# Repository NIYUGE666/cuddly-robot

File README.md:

# 波形合成电路 / Waveform Synthesis Circuit

NE555 + TL082，外接 ±12 V。NE555 产生约 2 kHz 时钟，经 CD4013 二分频、隔直和缓冲后得到可校准的 1 kHz、10 Vpp 方波。四路分别提取 1/3/5/7 kHz，调幅、移相后相加。

**Rev B 是已通过本地检查、需要实物校准的设计版本；尚未在嘉立创 EDA 专业版中实际导入验证。** 提供自包含 KiCad 可编辑源文件及 EAGLE XML 交换文件，不冒充嘉立创原生 `.epro` 工程。

| 文件 | 用途 |
|---|---|
| [导入说明](docs/IMPORT_EASYEDA_PRO.md) | 两种交换包、导入后核对项目、版本限制 |
| [设计及校准说明](docs/DESIGN.md) | 电路公式、元件参数、接口、22 个电位器的调试步骤 |
| [验证记录](docs/VALIDATION.md) | 已完成、自动通过、待验证及已知限制 |
| [原理图 PDF](docs/schematic.pdf) | 单张 A0 功能分区图；信号路径用实际导线连接 |
| [PCB 预览](docs/pcb.svg) | 双层，229 × 231 mm，全部插件安装 |
| [BOM](hardware/BOM.csv) / [分组 BOM](hardware/BOM_grouped.csv) | 逐项和采购分组；无未经核对的立创商品编号 |
| [KiCad 工程](hardware/waveform.kicad_pro) | KiCad 9.0.2；打开同目录的主原理图和 PCB |
| [EAGLE 原理图](hardware/waveform.sch) / [PCB](hardware/waveform.brd) | XML 交换格式，元件库内嵌 |
| [release](release/) | 两种导入 ZIP、制板输出 ZIP、校验和 |

Rev B 修正了旧版按元件清单排成网格的原理图：按信号流向排列四个通道，将 TL082 拆分为 A/B 放大单元和独立电源单元。PCB 铜线、过孔、封装位置和器件编号不变；根网络名称增加 `/` 前缀是 KiCad 单页局部网命名规则。

自动检查：ERC、DRC、未连接项、原理图/PCB 一致性均为 0 项；190 个封装、491 个引脚核对一致。EAGLE PCB 经 KiCad 的实际 EAGLE 导入器回读，489 个已连接引脚保持一致；2 个 CD4013 备用输出明确不连接。详细证据见 `validation/`。

波形计算采用 TL082 单极点近似，而非厂家 SPICE 模型或实测。四项傅里叶合成有 Gibbs 过冲，源方波 10 Vpp 对应的合成输出约 11.84 Vpp；如需要合成输出也恰为 10 Vpp，可统一缩放四路幅度，但不能消除有限谐波的过冲。

复现环境：系统 Python 3 + `pcbnew`、KiCad CLI 9、g++；分析脚本使用 Python 的 numpy/scipy/matplotlib。运行 `tools/validate.sh` 检查已有设计。**`tools/rebuild.sh` 会重新生成并覆盖本项目的生成文件，仅在确认没有手工编辑后使用。** 现有云任务已经隔离，无需另建 Git worktree。

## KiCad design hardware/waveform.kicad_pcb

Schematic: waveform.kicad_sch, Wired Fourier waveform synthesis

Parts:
C1, C2, C4, C5, C6, C7, C8, C9: 10n; C_Disc_D5.0mm_W2.5mm_P5.00mm
C3: 10u/25V; CP_Radial_D5.0mm_P2.00mm
C10, C11, C12, C13, C14, C15: 3.3n; C_Disc_D5.0mm_W2.5mm_P5.00mm
C16, C17, C18, C19, C20, C21: 2n; C_Disc_D5.0mm_W2.5mm_P5.00mm
C22, C23, C24, C25, C26, C27: 1.5n; C_Disc_D5.0mm_W2.5mm_P5.00mm
C28, C29: 47u/25V; CP_Radial_D5.0mm_P2.00mm
C30, C31, C32, C33, C34, C35, C36, C37, C38, C39, C40, C41, C42, C43, C44, C45, C46, C47, C48, C49, C50, C51, C52, C53, C54, C55, C56, C57, C58, C59: 100n; C_Disc_D5.0mm_W2.5mm_P5.00mm
J1, J2, J3, J4: PHASE_POLARITY; PinHeader_1x03_P2.54mm_Vertical
J5: POWER_12V; PinHeader_1x03_P2.54mm_Vertical
J6: WAVE_OUT; PinHeader_1x02_P2.54mm_Vertical
R1, R12, R13, R15, R16, R18, R19, R26, R27, R29, R30, R32, R33, R40, R41, R43, R44, R46, R47, R54, R55, R57, R58, R60, R61: 10k; R_Axial_DIN0207_L6.3mm_D2.5mm_P7.62mm_Horizontal
R2: 27k; R_Axial_DIN0207_L6.3mm_D2.5mm_P7.62mm_Horizontal
R3: 1M; R_Axial_DIN0207_L6.3mm_D2.5mm_P7.62mm_Horizontal
R4, R5, R62, R63, R64, R65, R66, R67, R68: 100k; R_Axial_DIN0207_L6.3mm_D2.5mm_P7.62mm_Horizontal
R6, R9, R20, R23, R34, R37, R48, R51: 220k; R_Axial_DIN0207_L6.3mm_D2.5mm_P7.62mm_Horizontal
R7, R10, R21, R24, R35, R38, R49, R52: 430; R_Axial_DIN0207_L6.3mm_D2.5mm_P7.62mm_Horizontal
R8, R11, R22, R25, R36, R39, R50, R53: 470k; R_Axial_DIN0207_L6.3mm_D2.5mm_P7.62mm_Horizontal
R14, R17, R28, R31, R42, R45, R56, R59, R69: 100; R_Axial_DIN0207_L6.3mm_D2.5mm_P7.62mm_Horizontal
RV1: 20k; Potentiometer_Bourns_3296W_Vertical
RV2: 100k; Potentiometer_Bourns_3296W_Vertical
RV3, RV4, RV8, RV9, RV13, RV14, RV18, RV19: 200; Potentiometer_Bourns_3296W_Vertical
RV5, RV6, RV10, RV11, RV15, RV16, RV20, RV21: 200k; Potentiometer_Bourns_3296W_Vertical
RV7, RV12, RV17, RV22: 10k; Potentiometer_Bourns_3296W_Vertical
TP1: CLOCK_2K; TestPoint_THTPad_D1.5mm_Drill0.7mm
TP2: SQ; TestPoint_THTPad_D1.5mm_Drill0.7mm
TP3: SQ_INV; TestPoint_THTPad_D1.5mm_Drill0.7mm
TP4: H1_BPF2; TestPoint_THTPad_D1.5mm_Drill0.7mm
TP5: H1_AP2; TestPoint_THTPad_D1.5mm_Drill0.7mm
TP6: H1_OUT; TestPoint_THTPad_D1.5mm_Drill0.7mm
TP7: H3_BPF2; TestPoint_THTPad_D1.5mm_Drill0.7mm
TP8: H3_AP2; TestPoint_THTPad_D1.5mm_Drill0.7mm
TP9: H3_OUT; TestPoint_THTPad_D1.5mm_Drill0.7mm
TP10: H5_BPF2; TestPoint_THTPad_D1.5mm_Drill0.7mm
TP11: H5_AP2; TestPoint_THTPad_D1.5mm_Drill0.7mm
TP12: H5_OUT; TestPoint_THTPad_D1.5mm_Drill0.7mm
TP13: H7_BPF2; TestPoint_THTPad_D1.5mm_Drill0.7mm
TP14: H7_AP2; TestPoint_THTPad_D1.5mm_Drill0.7mm
TP15: H7_OUT; TestPoint_THTPad_D1.5mm_Drill0.7mm
TP16: SUM_RAW; TestPoint_THTPad_D1.5mm_Drill0.7mm
TP17: OUT; TestPoint_THTPad_D1.5mm_Drill0.7mm
TP18: GND; TestPoint_THTPad_D1.5mm_Drill0.7mm
U1: NE555P; DIP-8_W7.62mm
U2: CD4013BE; DIP-14_W7.62mm
U3, U4, U5, U6, U7, U8, U9, U10, U11, U12, U13, U14, U15, U16: TL082CP; DIP-8_W7.62mm

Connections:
/AC_SQUARE: C3.2 (-), R3.1, RV2.1
/CLOCK_2K: TP1.1, U1.3 (OUT), U2.3 (CLK1)
/CTRL: C2.1, U1.5 (CTRL)
/DIGITAL_1K: C3.1 (+), U2.1 (Q1)
/DISCHARGE: R1.2, R2.1, U1.7 (DISCH)
/D_FEEDBACK: U2.2 (~Q1), U2.5 (D1)
/FREQ_R: R2.2, RV1.1
/GND: C1.2, C2.2, C8.2, C9.2, C14.2, C15.2, C20.2, C21.2, C26.2, C27.2, C28.2 (-), C29.1 (+), C30.2, C31.2, C32.2, C33.1, C34.2, C35.1, C36.2, C37.1, C38.2, C39.1, C40.2, C41.1, C42.2, C43.1, C44.2, C45.1, C46.2, C47.1, C48.2, C49.1, C50.2, C51.1, C52.2, C53.1, C54.2, C55.1, C56.2, C57.1, C58.2, C59.1, J5.2, J6.2, R3.2, RV2.3, RV3.2 (W), RV3.3, RV4.2 (W), RV4.3, RV7.3, RV8.2 (W), RV8.3, RV9.2 (W), RV9.3, RV12.3, RV13.2 (W), RV13.3, RV14.2 (W), RV14.3, RV17.3, RV18.2 (W), RV18.3, RV19.2 (W), RV19.3, RV22.3, TP18.1, U1.1 (GND), U2.4 (RESET1), U2.6 (SET1), U2.7 (VSS), U2.8 (SET2), U2.9 (D2), U2.11 (CLK2), U3.5 (+), U4.3 (+), U4.5 (+), U6.3 (+), U7.3 (+), U7.5 (+), U9.3 (+), U10.3 (+), U10.5 (+), U12.3 (+), U13.3 (+), U13.5 (+), U15.3 (+), U16.3 (+), U16.5 (+)
/H1_AMPLITUDE: RV7.2 (W), U6.5 (+)
/H1_AP1: R13.1, R15.1, R17.1, U5.1 (OUT)
/H1_AP2: J1.1, R16.1, R18.1, TP5.1, U5.7 (OUT)
/H1_APINV1: R12.2, R13.2, U5.2 (-)
/H1_APINV2: R15.2, R16.2, U5.6 (-)
/H1_BPF1: C4.2, R8.1, R9.1, U4.1 (OUT)
/H1_BPF2: C6.2, R11.1, R12.1, R14.1, TP4.1, U4.7 (OUT)
/H1_INV1: C5.2, R8.2, U4.2 (-)
/H1_INV2: C7.2, R11.2, U4.6 (-)
/H1_LP1: C8.1, RV5.2 (W), RV5.3, U5.3 (+)
/H1_LP2: C9.1, RV6.2 (W), RV6.3, U5.5 (+)
/H1_NEG: J1.3, R19.1, U6.1 (OUT)
/H1_NODE1: C4.1, C5.1, R6.2, R7.1
/H1_NODE2: C6.1, C7.1, R9.2, R10.1
/H1_OUT: R62.1, TP6.1, U6.6 (-), U6.7 (OUT)
/H1_PHR1: R14.2, RV5.1
/H1_PHR2: R17.2, RV6.1
/H1_POLINV: R18.2, R19.2, U6.2 (-)
/H1_SELECT: J1.2, RV7.1
/H1_TUNE1: R7.2, RV3.1
/H1_TUNE2: R10.2, RV4.1
/H3_AMPLITUDE: RV12.2 (W), U9.5 (+)
/H3_AP1: R27.1, R29.1, R31.1, U8.1 (OUT)
/H3_AP2: J2.1, R30.1, R32.1, TP8.1, U8.7 (OUT)
/H3_APINV1: R26.2, R27.2, U8.2 (-)
/H3_APINV2: R29.2, R30.2, U8.6 (-)
/H3_BPF1: C10.2, R22.1, R23.1, U7.1 (OUT)
/H3_BPF2: C12.2, R25.1, R26.1, R28.1, TP7.1, U7.7 (OUT)
/H3_INV1: C11.2, R22.2, U7.2 (-)
/H3_INV2: C13.2, R25.2, U7.6 (-)
/H3_LP1: C14.1, RV10.2 (W), RV10.3, U8.3 (+)
/H3_LP2: C15.1, RV11.2 (W), RV11.3, U8.5 (+)
/H3_NEG: J2.3, R33.1, U9.1 (OUT)
/H3_NODE1: C10.1, C11.1, R20.2, R21.1
/H3_NODE2: C12.1, C13.1, R23.2, R24.1
/H3_OUT: R63.1, TP9.1, U9.6 (-), U9.7 (OUT)
/H3_PHR1: R28.2, RV10.1
/H3_PHR2: R31.2, RV11.1
/H3_POLINV: R32.2, R33.2, U9.2 (-)
/H3_SELECT: J2.2, RV12.1
/H3_TUNE1: R21.2, RV8.1
/H3_TUNE2: R24.2, RV9.1
/H5_AMPLITUDE: RV17.2 (W), U12.5 (+)
/H5_AP1: R41.1, R43.1, R45.1, U11.1 (OUT)
/H5_AP2: J3.1, R44.1, R46.1, TP11.1, U11.7 (OUT)
/H5_APINV1: R40.2, R41.2, U11.2 (-)
/H5_APINV2: R43.2, R44.2, U11.6 (-)
/H5_BPF1: C16.2, R36.1, R37.1, U10.1 (OUT)
/H5_BPF2: C18.2, R39.1, R40.1, R42.1, TP10.1, U10.7 (OUT)
/H5_INV1: C17.2, R36.2, U10.2 (-)
/H5_INV2: C19.2, R39.2, U10.6 (-)
/H5_LP1: C20.1, RV15.2 (W), RV15.3, U11.3 (+)
/H5_LP2: C21.1, RV16.2 (W), RV16.3, U11.5 (+)
/H5_NEG: J3.3, R47.1, U12.1 (OUT)
/H5_NODE1: C16.1, C17.1, R34.2, R35.1
/H5_NODE2: C18.1, C19.1, R37.2, R38.1
/H5_OUT: R64.1, TP12.1, U12.6 (-), U12.7 (OUT)
/H5_PHR1: R42.2, RV15.1
/H5_PHR2: R45.2, RV16.1
/H5_POLINV: R46.2, R47.2, U12.2 (-)
/H5_SELECT: J3.2, RV17.1
/H5_TUNE1: R35.2, RV13.1
/H5_TUNE2: R38.2, RV14.1
/H7_AMPLITUDE: RV22.2 (W), U15.5 (+)
/H7_AP1: R55.1, R57.1, R59.1, U14.1 (OUT)
/H7_AP2: J4.1, R58.1, R60.1, TP14.1, U14.7 (OUT)
/H7_APINV1: R54.2, R55.2, U14.2 (-)
/H7_APINV2: R57.2, R58.2, U14.6 (-)
/H7_BPF1: C22.2, R50.1, R51.1, U13.1 (OUT)
/H7_BPF2: C24.2, R53.1, R54.1, R56.1, TP13.1, U13.7 (OUT)
/H7_INV1: C23.2, R50.2, U13.2 (-)
/H7_INV2: C25.2, R53.2, U13.6 (-)
/H7_LP1: C26.1, RV20.2 (W), RV20.3, U14.3 (+)
/H7_LP2: C27.1, RV21.2 (W), RV21.3, U14.5 (+)
/H7_NEG: J4.3, R61.1, U15.1 (OUT)
/H7_NODE1: C22.1, C23.1, R48.2, R49.1
/H7_NODE2: C24.1, C25.1, R51.2, R52.1
/H7_OUT: R65.1, TP15.1, U15.6 (-), U15.7 (OUT)
/H7_PHR1: R56.2, RV20.1
/H7_PHR2: R59.2, RV21.1
/H7_POLINV: R60.2, R61.2, U15.2 (-)
/H7_SELECT: J4.2, RV22.1
/H7_TUNE1: R49.2, RV18.1
/H7_TUNE2: R52.2, RV19.1
/OUT: J6.1, R69.2, TP17.1
/RESTORE_INV: R67.2, R68.2, U16.6 (-)
/SOURCE_WIPER: RV2.2 (W), U3.3 (+)
/SQ: R4.1, R6.1, R20.1, R34.1, R48.1, TP2.1, U3.1 (OUT), U3.2 (-)
/SQ_INV: R5.1, TP3.1, U3.7 (OUT)
/SQ_INV_IN: R4.2, R5.2, U3.6 (-)
/SUM_INV: R62.2, R63.2, R64.2, R65.2, R66.2, U16.2 (-)
/SUM_NEG: R66.1, R67.1, U16.1 (OUT)
/SUM_RAW: R68.1, R69.1, TP16.1, U16.7 (OUT)
/TIMING: C1.1, RV1.2 (W), RV1.3, U1.2 (TRIG), U1.6 (THRES)
/VCC: C28.1 (+), C30.1, C31.1, C32.1, C34.1, C36.1, C38.1, C40.1, C42.1, C44.1, C46.1, C48.1, C50.1, C52.1, C54.1, C56.1, C58.1, J5.1, R1.1, U1.4 (RESET), U1.8 (VCC), U2.10 (RESET2), U2.14 (VDD), U3.8 (V+), U4.8 (V+), U5.8 (V+), U6.8 (V+), U7.8 (V+), U8.8 (V+), U9.8 (V+), U10.8 (V+), U11.8 (V+), U12.8 (V+), U13.8 (V+), U14.8 (V+), U15.8 (V+), U16.8 (V+)
/VEE: C29.2 (-), C33.2, C35.2, C37.2, C39.2, C41.2, C43.2, C45.2, C47.2, C49.2, C51.2, C53.2, C55.2, C57.2, C59.2, J5.3, U3.4 (V-), U4.4 (V-), U5.4 (V-), U6.4 (V-), U7.4 (V-), U8.4 (V-), U9.4 (V-), U10.4 (V-), U11.4 (V-), U12.4 (V-), U13.4 (V-), U14.4 (V-), U15.4 (V-), U16.4 (V-)

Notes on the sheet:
NE555 + TL082 FOURIER WAVEFORM SYNTHESIS — Rev B wired schematic
Regulated +12 V / GND / -12 V. Signal wires are drawn explicitly. All labels are single-sheet local nets.
SOURCE: 2 kHz clock / divide by two / DC blocking / 10 Vpp calibration
1 kHz: TWO MFB BANDPASS SECTIONS -> TWO ALL-PASS SECTIONS -> POLARITY -> AMPLITUDE
ONE shunt: default 2-3
3 kHz: TWO MFB BANDPASS SECTIONS -> TWO ALL-PASS SECTIONS -> POLARITY -> AMPLITUDE
5 kHz: TWO MFB BANDPASS SECTIONS -> TWO ALL-PASS SECTIONS -> POLARITY -> AMPLITUDE
7 kHz: TWO MFB BANDPASS SECTIONS -> TWO ALL-PASS SECTIONS -> POLARITY -> AMPLITUDE
SUM AND OUTPUT
REGULATED +/-12 V INPUT
C29 positive terminal = GND
ANALOG POWER AND LOCAL BYPASS: 100 nF at each supply pin

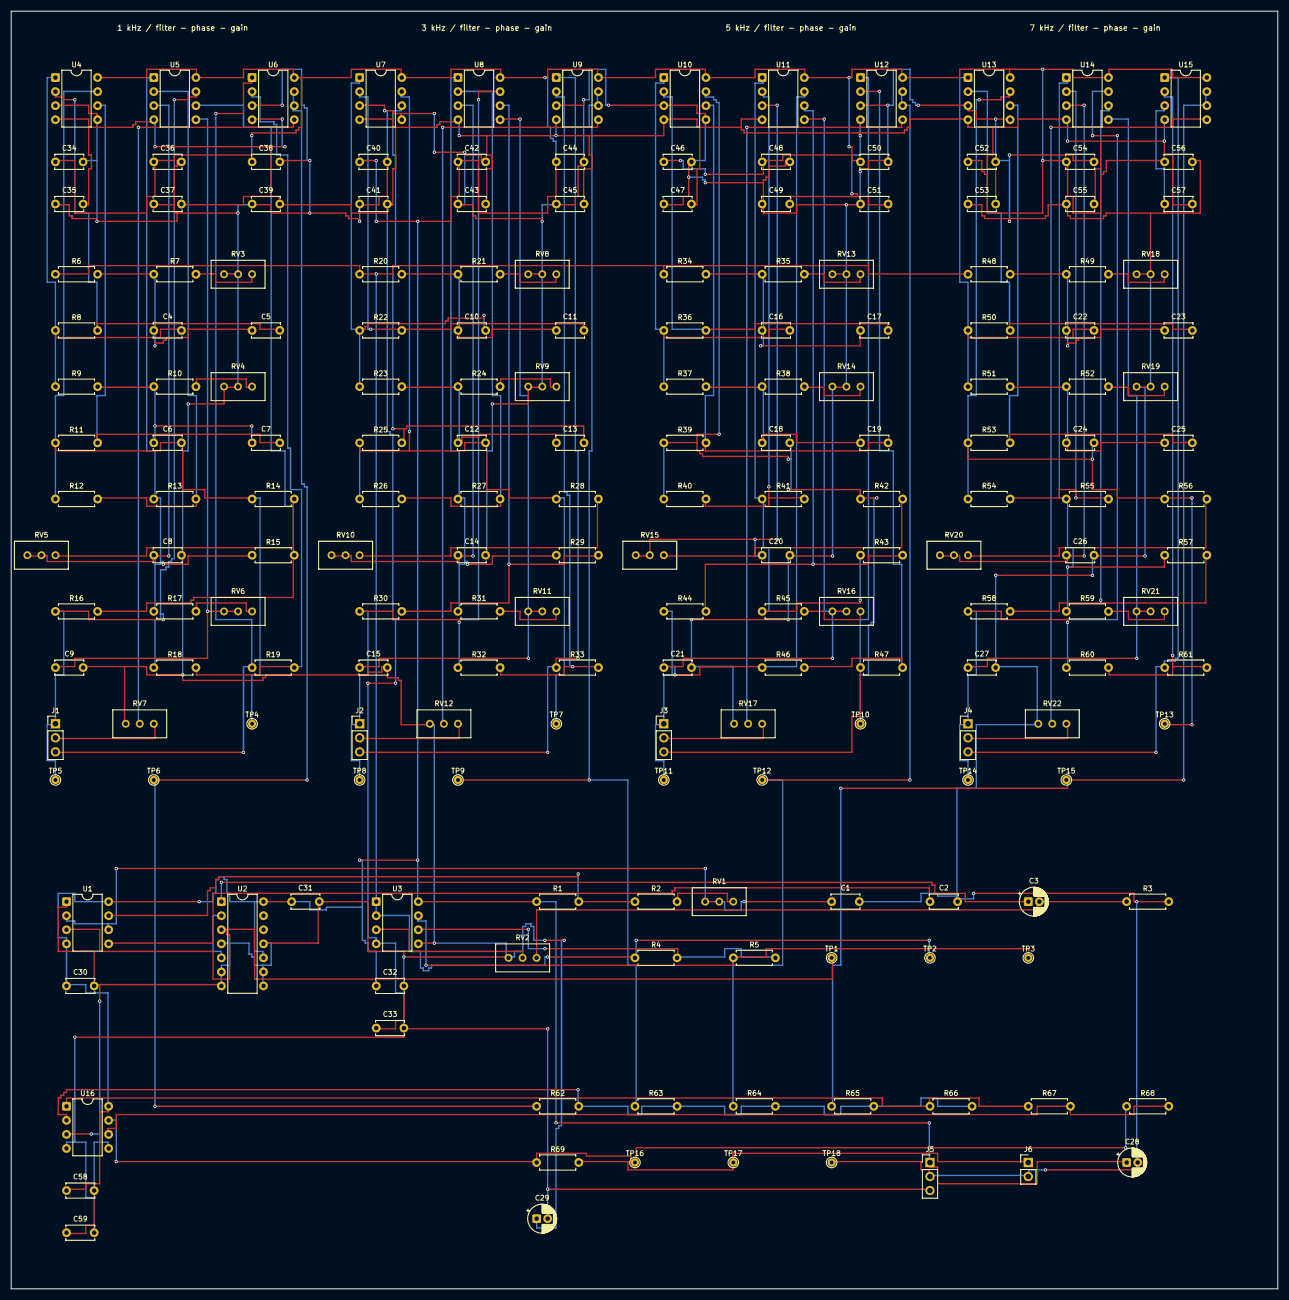
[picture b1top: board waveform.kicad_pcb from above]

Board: 2 copper layers, 229.0 x 231.0 mm, 190 parts (0 on the bottom side), 104 nets.

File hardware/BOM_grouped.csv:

References,Quantity,Value,Type,Footprint,Purchasing_notes
U2,1,CD4013BE,4013,Waveform:DIP-14_W7.62mm,"Through-hole DIP, 7.62mm row spacing; do not substitute a different pinout"
C22 C23 C24 C25 C26 C27,6,1.5n,C,Waveform:C_Disc_D5.0mm_W2.5mm_P5.00mm,5mm pitch; BPF/all-pass: 1% C0G/film; bypass: X7R permitted
C30 C31 C32 C33 C34 C35 C36 C37 C38 C39 C40 C41 C42 C43 C44 C45 C46 C47 C48 C49 C50 C51 C52 C53 C54 C55 C56 C57 C58 C59,30,100n,C,Waveform:C_Disc_D5.0mm_W2.5mm_P5.00mm,5mm pitch; BPF/all-pass: 1% C0G/film; bypass: X7R permitted
C1 C2 C4 C5 C6 C7 C8 C9,8,10n,C,Waveform:C_Disc_D5.0mm_W2.5mm_P5.00mm,5mm pitch; BPF/all-pass: 1% C0G/film; bypass: X7R permitted
C16 C17 C18 C19 C20 C21,6,2n,C,Waveform:C_Disc_D5.0mm_W2.5mm_P5.00mm,5mm pitch; BPF/all-pass: 1% C0G/film; bypass: X7R permitted
C10 C11 C12 C13 C14 C15,6,3.3n,C,Waveform:C_Disc_D5.0mm_W2.5mm_P5.00mm,5mm pitch; BPF/all-pass: 1% C0G/film; bypass: X7R permitted
J6,1,WAVE_OUT,CONN2,Waveform:PinHeader_1x02_P2.54mm_Vertical,2.54mm through-hole header; phase headers additionally require ONE shunt each
J1 J2 J3 J4,4,PHASE_POLARITY,CONN3,Waveform:PinHeader_1x03_P2.54mm_Vertical,2.54mm through-hole header; phase headers additionally require ONE shunt each
J5,1,POWER_12V,CONN3,Waveform:PinHeader_1x03_P2.54mm_Vertical,2.54mm through-hole header; phase headers additionally require ONE shunt each
C3,1,10u/25V,CP,Waveform:CP_Radial_D5.0mm_P2.00mm,"25V minimum, D5mm P2mm; verify purchased body diameter and polarity"
C28 C29,2,47u/25V,CP,Waveform:CP_Radial_D5.0mm_P2.00mm,"25V minimum, D5mm P2mm; verify purchased body diameter and polarity"
U1,1,NE555P,NE555,Waveform:DIP-8_W7.62mm,"Through-hole DIP, 7.62mm row spacing; do not substitute a different pinout"
RV2,1,100k,POT,Waveform:Potentiometer_Bourns_3296W_Vertical,"Bourns 3296W vertical, value code 104; verify pinout 1/2(wiper)/3"
RV7 RV12 RV17 RV22,4,10k,POT,Waveform:Potentiometer_Bourns_3296W_Vertical,"Bourns 3296W vertical, value code 103; verify pinout 1/2(wiper)/3"
RV3 RV4 RV8 RV9 RV13 RV14 RV18 RV19,8,200,POT,Waveform:Potentiometer_Bourns_3296W_Vertical,"Bourns 3296W vertical, value code 201; verify pinout 1/2(wiper)/3"
RV5 RV6 RV10 RV11 RV15 RV16 RV20 RV21,8,200k,POT,Waveform:Potentiometer_Bourns_3296W_Vertical,"Bourns 3296W vertical, value code 204; verify pinout 1/2(wiper)/3"
RV1,1,20k,POT,Waveform:Potentiometer_Bourns_3296W_Vertical,"Bourns 3296W vertical, value code 203; verify pinout 1/2(wiper)/3"
R14 R17 R28 R31 R42 R45 R56 R59 R69,9,100,R,Waveform:R_Axial_DIN0207_L6.3mm_D2.5mm_P7.62mm_Horizontal,"DIN0207 7.62mm pitch; 0.1% recommended for matched gains, 1% otherwise"
R4 R5 R62 R63 R64 R65 R66 R67 R68,9,100k,R,Waveform:R_Axial_DIN0207_L6.3mm_D2.5mm_P7.62mm_Horizontal,"DIN0207 7.62mm pitch; 0.1% recommended for matched gains, 1% otherwise"
R1 R12 R13 R15 R16 R18 R19 R26 R27 R29 R30 R32 R33 R40 R41 R43 R44 R46 R47 R54 R55 R57 R58 R60 R61,25,10k,R,Waveform:R_Axial_DIN0207_L6.3mm_D2.5mm_P7.62mm_Horizontal,"DIN0207 7.62mm pitch; 0.1% recommended for matched gains, 1% otherwise"
R3,1,1M,R,Waveform:R_Axial_DIN0207_L6.3mm_D2.5mm_P7.62mm_Horizontal,"DIN0207 7.62mm pitch; 0.1% recommended for matched gains, 1% otherwise"
R6 R9 R20 R23 R34 R37 R48 R51,8,220k,R,Waveform:R_Axial_DIN0207_L6.3mm_D2.5mm_P7.62mm_Horizontal,"DIN0207 7.62mm pitch; 0.1% recommended for matched gains, 1% otherwise"
R2,1,27k,R,Waveform:R_Axial_DIN0207_L6.3mm_D2.5mm_P7.62mm_Horizontal,"DIN0207 7.62mm pitch; 0.1% recommended for matched gains, 1% otherwise"
R7 R10 R21 R24 R35 R38 R49 R52,8,430,R,Waveform:R_Axial_DIN0207_L6.3mm_D2.5mm_P7.62mm_Horizontal,"DIN0207 7.62mm pitch; 0.1% recommended for matched gains, 1% otherwise"
R8 R11 R22 R25 R36 R39 R50 R53,8,470k,R,Waveform:R_Axial_DIN0207_L6.3mm_D2.5mm_P7.62mm_Horizontal,"DIN0207 7.62mm pitch; 0.1% recommended for matched gains, 1% otherwise"
U3 U4 U5 U6 U7 U8 U9 U10 U11 U12 U13 U14 U15 U16,14,TL082CP,TL082,Waveform:DIP-8_W7.62mm,"Through-hole DIP, 7.62mm row spacing; do not substitute a different pinout"
TP1,1,CLOCK_2K,TP,Waveform:TestPoint_THTPad_D1.5mm_Drill0.7mm,"Bare PCB test pad, no component purchase required"
TP18,1,GND,TP,Waveform:TestPoint_THTPad_D1.5mm_Drill0.7mm,"Bare PCB test pad, no component purchase required"
TP5,1,H1_AP2,TP,Waveform:TestPoint_THTPad_D1.5mm_Drill0.7mm,"Bare PCB test pad, no component purchase required"
TP4,1,H1_BPF2,TP,Waveform:TestPoint_THTPad_D1.5mm_Drill0.7mm,"Bare PCB test pad, no component purchase required"
TP6,1,H1_OUT,TP,Waveform:TestPoint_THTPad_D1.5mm_Drill0.7mm,"Bare PCB test pad, no component purchase required"
TP8,1,H3_AP2,TP,Waveform:TestPoint_THTPad_D1.5mm_Drill0.7mm,"Bare PCB test pad, no component purchase required"
TP7,1,H3_BPF2,TP,Waveform:TestPoint_THTPad_D1.5mm_Drill0.7mm,"Bare PCB test pad, no component purchase required"
TP9,1,H3_OUT,TP,Waveform:TestPoint_THTPad_D1.5mm_Drill0.7mm,"Bare PCB test pad, no component purchase required"
TP11,1,H5_AP2,TP,Waveform:TestPoint_THTPad_D1.5mm_Drill0.7mm,"Bare PCB test pad, no component purchase required"
TP10,1,H5_BPF2,TP,Waveform:TestPoint_THTPad_D1.5mm_Drill0.7mm,"Bare PCB test pad, no component purchase required"
TP12,1,H5_OUT,TP,Waveform:TestPoint_THTPad_D1.5mm_Drill0.7mm,"Bare PCB test pad, no component purchase required"
TP14,1,H7_AP2,TP,Waveform:TestPoint_THTPad_D1.5mm_Drill0.7mm,"Bare PCB test pad, no component purchase required"
TP13,1,H7_BPF2,TP,Waveform:TestPoint_THTPad_D1.5mm_Drill0.7mm,"Bare PCB test pad, no component purchase required"
TP15,1,H7_OUT,TP,Waveform:TestPoint_THTPad_D1.5mm_Drill0.7mm,"Bare PCB test pad, no component purchase required"
TP17,1,OUT,TP,Waveform:TestPoint_THTPad_D1.5mm_Drill0.7mm,"Bare PCB test pad, no component purchase required"
TP2,1,SQ,TP,Waveform:TestPoint_THTPad_D1.5mm_Drill0.7mm,"Bare PCB test pad, no component purchase required"
TP3,1,SQ_INV,TP,Waveform:TestPoint_THTPad_D1.5mm_Drill0.7mm,"Bare PCB test pad, no component purchase required"
TP16,1,SUM_RAW,TP,Waveform:TestPoint_THTPad_D1.5mm_Drill0.7mm,"Bare PCB test pad, no component purchase required"
J1 J2 J3 J4,4,2.54mm shunt,ACCESSORY,,"One shunt per phase header, default pins 2-3"
U1 U3-U16,15,DIP-8 socket (optional),ACCESSORY,,7.62mm width
U2,1,DIP-14 socket (optional),ACCESSORY,,7.62mm width

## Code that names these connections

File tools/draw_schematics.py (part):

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text('SOURCE: 2 kHz clock / divide by two / DC blocking / 10 Vpp calibration',65,34,2)
# Source NE555 and its timing loop.
place('U1',180,75);place('U2',320,75)
r1=two('R','VCC','DISCHARGE');place(r1,220,45,270);port('VCC',pin(r1,1),'up')
wire('DISCHARGE',pin(r1,2),(g(220),pin('U1',7)[1]),pin('U1',7))
r2=two('R','DISCHARGE','FREQ_R');place(r2,220,95,270);wire('DISCHARGE',(g(220),pin('U1',7)[1]),pin(r2,1));dot('DISCHARGE',(g(220),pin('U1',7)[1]))
place('RV1',220,120,270);chain('FREQ_R',pin(r2,2),pin('RV1',1));strap('RV1')
place('C1',140,125,270);ty=g(105.41);tx=g(140)
wire('TIMING',pin('RV1',3),(pin('RV1',3)[0],ty),(tx,ty),pin('C1',1));port('GND',pin('C1',2))
wire('TIMING',(tx,ty),(tx,pin('U1',2)[1]),pin('U1',2));dot('TIMING',(tx,ty))
wire('TIMING',pin('U1',6),(tx,pin('U1',6)[1]));dot('TIMING',(tx,pin('U1',6)[1]))
port('VCC',pin('U1',8),'up');port('VCC',pin('U1',4),'left');port('GND',pin('U1',1))
place('C2',155,110,270);wire('CTRL',pin('U1',5),(pin('C2',1)[0],pin('U1',5)[1]),pin('C2',1));port('GND',pin('C2',2))
wire('CLOCK_2K',pin('U1',3),(g(250),pin('U1',3)[1]),(g(250),pin('U2',3)[1]),pin('U2',3))
place('TP1',250,45);wire('CLOCK_2K',pin('TP1',1),(g(250),pin('U2',3)[1]));dot('CLOCK_2K',(g(250),pin('U2',3)[1]))
port('VCC',pin('U2',14),'up');port('GND',pin('U2',7))
wire('D_FEEDBACK',pin('U2',2),(g(353.06),pin('U2',2)[1]),(g(353.06),g(39.37)),(g(290.83),g(39.37)),(g(290.83),pin('U2',5)[1]),pin('U2',5))
for no in [4,6,8,9,11]:port('GND',pin('U2',no),'right' if no==8 else 'left')
port('VCC',pin('U2',10),'right')
for no in [12,13]:
 x,y=pin('U2',no);items.append(f'(no_connect (at {fmt(x)} {fmt(y)}) (uuid "{idnext("nc")}"))')
place('C3',390,pin('U2',1)[1]);chain('DIGITAL_1K',pin('U2',1),pin('C3',1))
place('R3',410,100,270);place('RV2',440,100,270)
ay=pin('C3',2)[1];wire('AC_SQUARE',pin('C3',2),(g(440),ay),pin('RV2',1))
wire('AC_SQUARE',pin('R3',1),(g(410),ay));dot('AC_SQUARE',(g(410),ay))
port('GND',pin('R3',2));port('GND',pin('RV2',3))
buffin,sq=follower('U3',1,530,100);chain('SOURCE_WIPER',pin('RV2',2),buffin)
place('TP2',sq[0],80);wire('SQ',pin('TP2',1),sq);dot('SQ',sq)
ii,oo=inverter('U3',2,700,100,'SQ','SQ_INV');chain('SQ',sq,ii)
place('TP3',750,100);chain('SQ_INV',oo,pin('TP3',1))
wire('SQ',sq,(sq[0],g(150)),(g(45.72),g(150)),(g(45.72),g(682.54)))
# Four rows, each with the same signal flow from left to right.
outpoints={}
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opblock('U16',1,1120,750);pl,mi,oo=plusminus('U16',1);sumy=pin('U16',mi)[1]
for k,n in enumerate([1,3,5,7]):
 net=f'H{n}_OUT';x=g(1016+25.4*k);rr=two('R',net,'SUM_INV');place(rr,x,720,270)
 pt=outpoints[n];wire(net,pt,(x,pt[1]),pin(rr,1));wire('SUM_INV',pin(rr,2),(x,sumy),pin('U16',mi));dot('SUM_INV',(x,sumy))
port('GND',pin('U16',pl),'left');rf=component('R','SUM_NEG','SUM_INV',1145,730,180)
wire('SUM_INV',pin('U16',mi),(pin('U16',mi)[0],g(730)),pin(rf,2));dot('SUM_INV',pin('U16',mi))
sn=(g(1153.16),g(750));wire('SUM_NEG',pin('U16',oo),sn,(sn[0],g(730)),pin(rf,1));dot('SUM_NEG',sn)
iin,raw=inverter('U16',2,1120,790,'SUM_NEG','SUM_RAW');wire('SUM_NEG',sn,(sn[0],g(770)),(g(1050.29),g(770)),(g(1050.29),iin[1]),iin)
rr=two('R','SUM_RAW','OUT');place(rr,1166,790);chain('SUM_RAW',raw,pin(rr,1))
place('J6',1176,805,180);wire('OUT',pin(rr,2),(g(1182.37),g(790)),(g(1182.37),pin('J6',1)[1]),pin('J6',1));port('GND',pin('J6',2),'left')
for ref,net,pt,x,y in [('TP16','SUM_RAW',raw,1145,775),('TP17','OUT',pin(rr,2),1170,775)]:
 place(ref,x,y);chain(net,pin(ref,1),pt);dot(net,pt)
place('TP18',1025,800);port('GND',pin('TP18',1))

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text('ANALOG POWER AND LOCAL BYPASS: 100 nF at each supply pin',50,750,1.5)
vccy=g(767.08);veey=g(813.0)
wire('VCC',(g(45),vccy),(g(70+13*66.04),vccy));wire('VEE',(g(45),veey),(g(70+13*66.04+20.32),veey))
label('VCC',(g(45),vccy),True);label('VEE',(g(45),veey),True)
for i in range(3,17):
 x=g(70+(i-3)*66.04);y=g(790);ref=f'U{i}';place(ref,x,y,unit=3)
 wire('VCC',pin(ref,8,3),(x,vccy));dot('VCC',(x,vccy));wire('VEE',pin(ref,4,3),(x,veey));dot('VEE',(x,veey))
 cp=next(p['ref'] for p in parts.values() if p['note']==f'Place at {ref} supply pin');cn=next(p['ref'] for p in parts.values() if p['note']==f'Place at {ref} negative supply pin')
 place(cp,x-20.32,y,270);place(cn,x+20.32,y,270)
 wire('VCC',pin(cp,1),(pin(cp,1)[0],vccy));dot('VCC',(pin(cp,1)[0],vccy));port('GND',pin(cp,2))
 wire('VEE',pin(cn,2),(pin(cn,2)[0],veey));dot('VEE',(pin(cn,2)[0],veey));port('GND',pin(cn,1),'up')

# Add explicit intersections only for same-net T nodes. Different-net crossings
# intentionally have no dot. Reject a node touched by differently named nets.
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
